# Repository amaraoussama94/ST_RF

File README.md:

# ST_RF
STM32_RF_Nordic/
-stm32l432kb
Nordic_NRF24L01

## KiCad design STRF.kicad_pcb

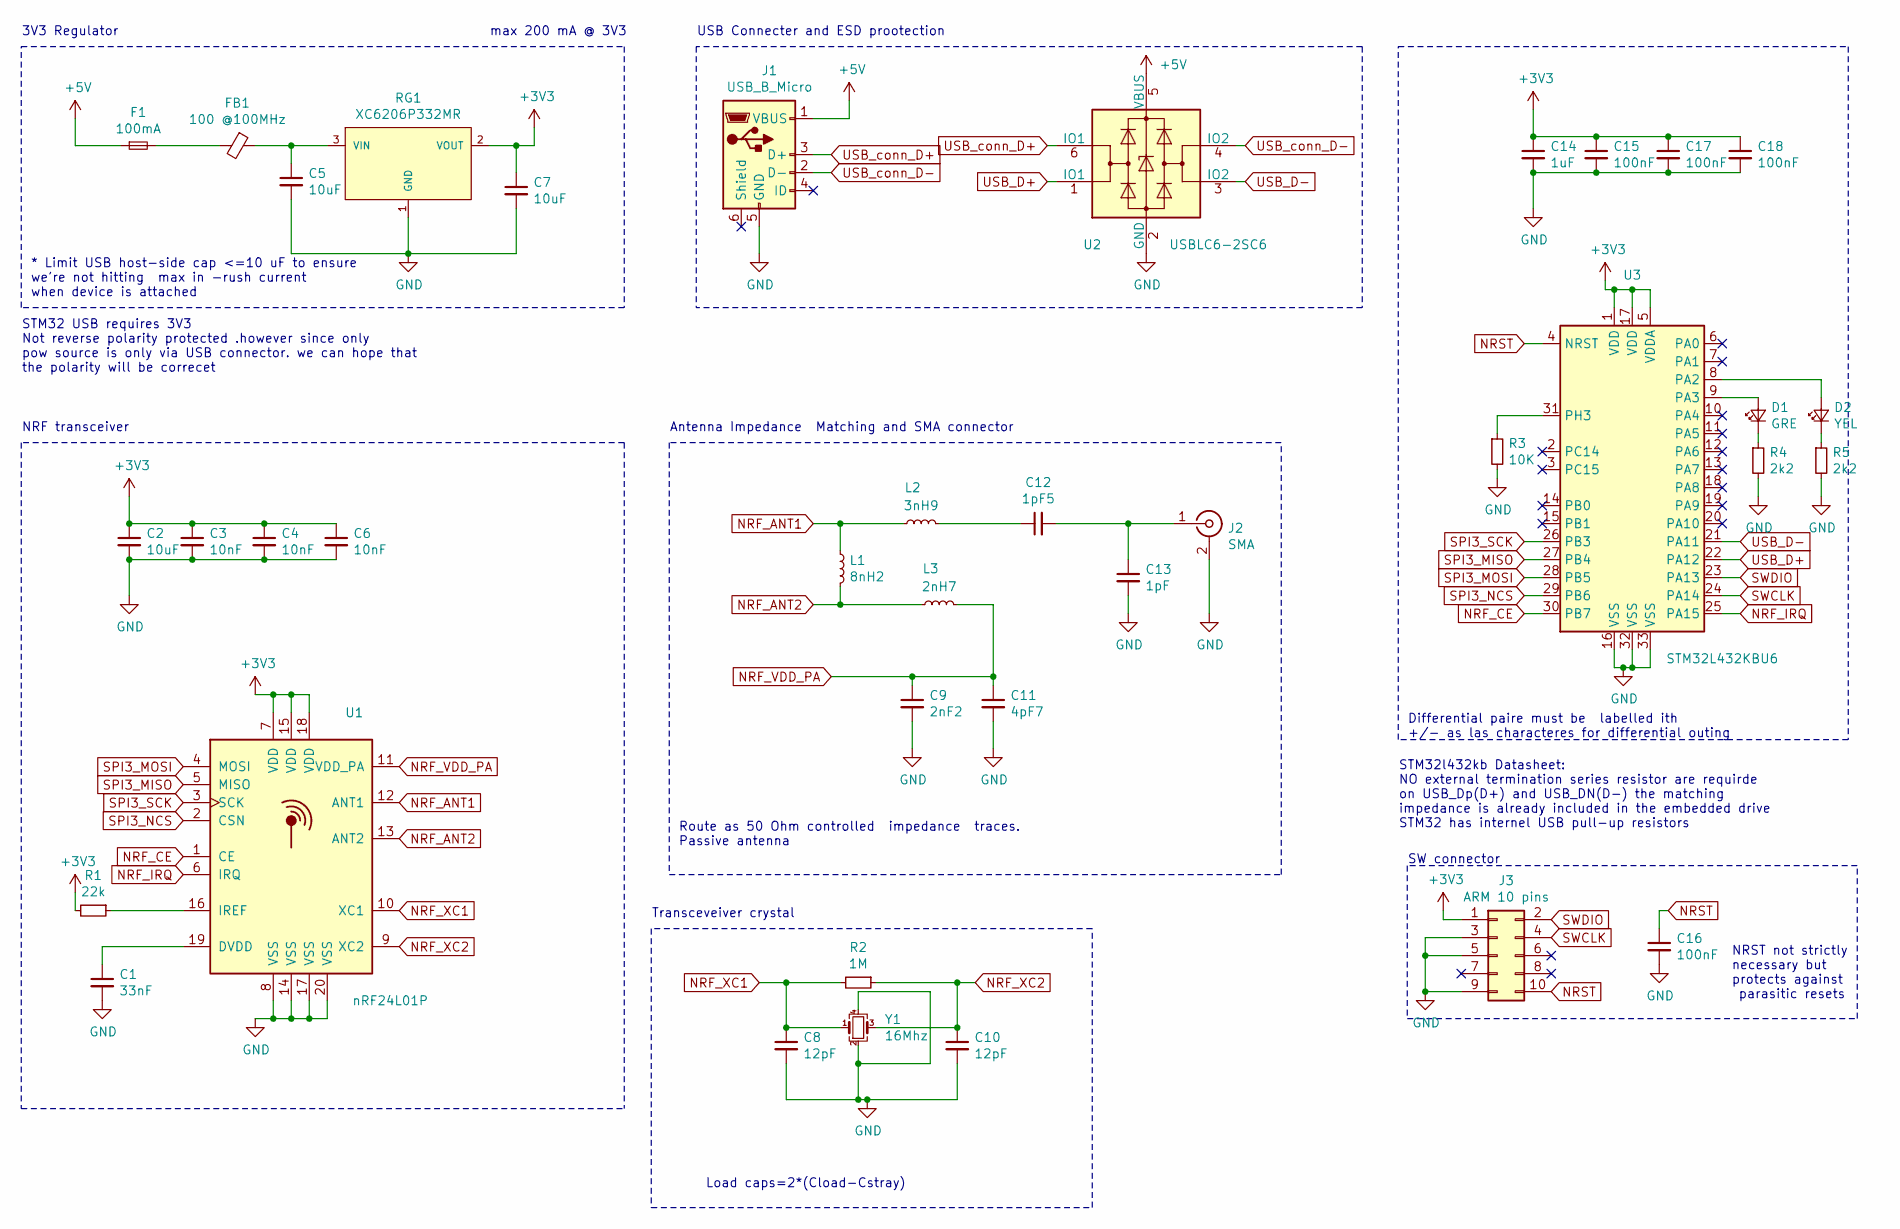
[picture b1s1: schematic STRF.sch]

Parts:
C1: 33nF; C_0402_1005Metric
C2, C5, C7: 10uF; C_0603_1608Metric
C3, C4, C6: 10nF; C_0402_1005Metric
C8, C10: 12pF; C_0402_1005Metric
C9: 2nF2; C_0402_1005Metric
C11: 4pF7; C_0402_1005Metric
C12: 1pF5; C_0402_1005Metric
C13: 1pF; C_0402_1005Metric
C14: 1uF; C_0402_1005Metric
C15, C16, C17, C18: 100nF; C_0402_1005Metric
D1: GRE; LED_0603_1608Metric
D2: YEL; LED_0603_1608Metric
F1: 100mA; Fuse_1206_3216Metric
FB1: 100 @100MHz; L_0805_2012Metric
J1: USB_B_Micro; USB_Micro-B_Molex-105017-0001
J2: SMA; SMA_Samtec_SMA-J-P-H-ST-EM1_EdgeMount
J3: ARM 10 pins; PinHeader_2x05_P1.27mm_Vertical
L1: 8nH2; L_0402_1005Metric
L2: 3nH9; L_0402_1005Metric
L3: 2nH7; L_0402_1005Metric
R1: 22k; R_0402_1005Metric
R2: 1M; R_0402_1005Metric
R3: 10K; R_0402_1005Metric
R4, R5: 2k2; R_0603_1608Metric
RG1: XC6206P332MR; SOT-23; Dropout Voltage 250mV; voltage 3.3V; mouser part number 865-XC6206P332MR-G
U1: nRF24L01P; QFN-20-1EP_4x4mm_P0.5mm_EP2.5x2.5mm
U2: USBLC6-2SC6; TSOT-23-6
U3: STM32L432KBU6; QFN-32-1EP_5x5mm_P0.5mm_EP3.45x3.45mm
Y1: 16Mhz; Crystal_SMD_3225-4Pin_3.2x2.5mm

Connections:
+3V3: C2.1, C3.1, C4.1, C6.1, C7.1, C14.1, C15.1, C17.1, C18.1, J3.1, R1.2, RG1.2 (VOUT), U1.7 (VDD), U1.15 (VDD), U1.18 (VDD), U3.1 (VDD), U3.5 (VDDA), U3.17 (VDD)
+5V: F1.1, J1.1 (VBUS), U2.5 (VBUS)
GND: C1.2, C2.2, C3.2, C4.2, C5.2, C6.2, C7.2, C8.2, C9.2, C10.2, C11.2, C13.2, C14.2, C15.2, C16.2, C17.2, C18.2, J1.5 (GND), J2.2 (Ext), J3.3, J3.5, J3.9, R3.2, R4.2, R5.2, RG1.1 (GND), U1.8 (VSS), U1.14 (VSS), U1.17 (VSS), U1.20 (VSS), U2.2 (GND), U3.16 (VSS), U3.32 (VSS), U3.33 (VSS), Y1.2, Y1.4
NRF_ANT1: L1.1, L2.1, U1.12 (ANT1)
NRF_ANT2: L1.2, L3.1, U1.13 (ANT2)
NRF_CE: U1.1 (CE), U3.30 (PB7)
NRF_IRQ: U1.6 (IRQ), U3.25 (PA15)
NRF_VDD_PA: C9.1, C11.1, L3.2, U1.11 (VDD_PA)
NRF_XC1: C8.1, R2.2, U1.10 (XC1), Y1.1
NRF_XC2: C10.1, R2.1, U1.9 (XC2), Y1.3
NRST: C16.1, J3.10, U3.4 (NRST)
unnamed: C1.1, U1.19 (DVDD)
unnamed: C5.1, FB1.1, RG1.3 (VIN)
unnamed: C12.1, L2.2
unnamed: C12.2, C13.1, J2.1 (In)
unnamed: D1.1 (K), R4.1
unnamed: D1.2 (A), U3.9 (PA3)
unnamed: D2.1 (K), R5.1
unnamed: D2.2 (A), U3.8 (PA2)
unnamed: F1.2, FB1.2
unnamed: R1.1, U1.16 (IREF)
unnamed: R3.1, U3.31 (PH3)
SPI3_MISO: U1.5 (MISO), U3.27 (PB4)
SPI3_MOSI: U1.4 (MOSI), U3.28 (PB5)
SPI3_NCS: U1.2 (CSN), U3.29 (PB6)
SPI3_SCK: U1.3 (SCK), U3.26 (PB3)
SWCLK: J3.4, U3.24 (PA14)
SWDIO: J3.2, U3.23 (PA13)
USB_D+: U2.1 (IO1), U3.22 (PA12)
USB_D-: U2.3 (IO2), U3.21 (PA11)
USB_conn_D+: J1.3 (D+), U2.6 (IO1)
USB_conn_D-: J1.2 (D-), U2.4 (IO2)

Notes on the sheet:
3V3 Regulator
max 200 mA @ 3V3
* Limit USB host-side cap <=10 uF to ensure we're not hitting max in -rush current when device is attached
STM32 USB requires 3V3 Not reverse polarity protected .however since only pow source is only via USB connector. we can hope that the polarity will be correcet
USB Connecter and ESD prootection
Differential paire must be labelled ith +/- as las characteres for differential outing
STM32l432kb Datasheet: NO external termination series resistor are requirde on USB_Dp(D+) and USB_DN(D-) the matching impedance is already included in the embedded drive STM32 has internel USB pull-up resistors
SW connector
NRST not strictly necessary but protects against parasitic resets
NRF transceiver
Transceveiver crystal
Load caps=2*(Cload-Cstray)
Antenna Impedance Matching and SMA connector
Route as 50 Ohm controlled impedance traces. Passive antenna

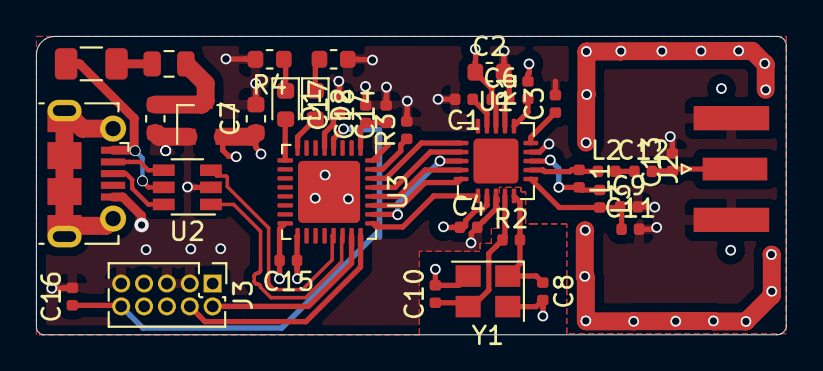
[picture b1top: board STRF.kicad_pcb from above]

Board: 4 copper layers, 41.7 x 16.6 mm, 38 parts (0 on the bottom side), 32 nets.
